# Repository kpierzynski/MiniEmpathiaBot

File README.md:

# RoboBond
## Empatyczny rój robotów

| Mobilny rój robotów |
|:-:|
||

### Motywacja
Celem projektu jest opracowanie drugiej generacji empatycznego roju robotów, umożliwiającej przeprowadzanie fizycznych eksperymentów wygodniej, szybciej i na szerszą skalę. Celem badawczym jest analiza algorytmów sztucznej empatii na zminiaturyzowanej generacji roju robotów.

### Opis
Projekt "Rój Empatycznych Robotów" polega na stworzeniu zaawansowanej grupy robotów, która będzie zdolna do interakcji i współpracy, odzwierciedlając przy tym podstawowe instynkty ludzkie, aby efektywnie rozwiązywać zadane problemy. Przyjęcie perspektywy innej osoby i próba zrozumienia jej punktu widzenia znaczenie poprawia współpracę oraz wpływa na osiągnięte wyniki. Roboty dzięki modułowi sztucznej empatii, będą mogły podejmować decyzje w oparciu o stan sąsiednich robotów, pozwala to na stworzenie bardziej efektywnych strategii i szybsze osiągnięcie globalnego celu.

Do przeprowadzenia eksperymentów walidujących użycie algorytmów sztucznej empatii, stworzone zostały dwa symulatory oraz fizyczna platforma mobilnych robotów.

### Zastosowania
- Platforma badawcza dla naukowców do weryfikacji nowych algorytmów sztucznej empatii,
- Środowisko dla nauczycieli wspierające dydaktykę z zakresu sztucznej inteligencji,
- Infrastruktura do testowania nowych ścieżek automatyzacji i robotyzacji w przedsiębiorstwach,
- ... oraz wiele innych.

### Zawartość
W repozytorium znajdują się:
- Symulatory
    - `simulators/RL_ROS_Robots`
    - `simulators/Simpathy`
- Projekt mobilnych robotów
    - `kicad_workspace/bottom` - schemat elektroniczny PCB oraz opis konstrukcji
    - `code/STM32` - kod źródłowy dolnego niskopoziomowego mikrokontrolera robota
    - `code/PI` - kod źródłowy implementujący scenariusz empatyczny 
    - `cad_models` - modele 3d części robota

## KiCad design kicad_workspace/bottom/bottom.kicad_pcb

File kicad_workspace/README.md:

# Empatyczny robot, iteracja druga

## Obecna konstrukcja PCB
Widok gory | Widok spodu
-- | --
 | 

## Architektura robota

Ze względu na minimalizację wymiarów robota, jego konstrukcja przewiduje dwie połączone nad sobą płytki drukowane. Dolna płytka będzie odpowiedzialna za interakcję z otoczeniem, a górna, za przetwarzanie informacji i podejmowanie decyzji. 

Poruszanie się robota w przestrzeni będzie realizowane przy pomocy dwóch miniaturowych silników z przekładniami firmy Pololu. Każdy z nich wyposażony jest w enkoder magnetyczny na bazie czujników efektu Hall’a TLE4946-2K, specjalnie zaprojektowanych do tego scenariusza. Obrót silników będzie dodatkowo nadzorowany przez czujniki prądu, jeden na każdy silnik, aby uzyskać dokładne sterowanie prędkością obrotową. W celu wyeliminowania strat na typowych czujnikach prądu z shunt resistor, można użyć układu, który mierzy prąd w oparciu o efekt Hall’a. Przykładem takich sensorów są ACS712 lub ACS724. Do zasilania silników jako układ wykonawczy zostanie wykorzystany DRV8833. Ten sterownik umożliwia obsługę dwóch silników i charakteryzuje się tym, że wymaga jedynie dwóch linii sterujących na silnik do regulacji prędkości i kierunku obrotu, a także jest prosty w obsłudze za pomocą sprzętowych Timer'ów w mikrokontrolerze. 

Aby zapewnić robotowi precyzyjną orientację w terenie, zostanie wyposażony w zintegrowany układ BNO055, składający się z akcelerometru, żyroskopu oraz magnetometru firmy Bosch. Układ ten będzie wspomagać algorytmy ruchu robota, aby osiągnąć maksymalną precyzję jego manewrów. Dodatkowo, sensory VL53L0X dostarczą informację o odległości przeszkód znajdujących się przed robotem. Zastosowanie tych sensorów wprowadza zwiększoną złożoność zarówno konstrukcji płytki, jak i algorytmów sterujących w porównaniu do tradycyjnych przycisków i krańcówek. Niemniej jednak ta zmiana przyczynia się do redukcji kontaktu mechanicznego z otoczeniem, co przekłada się na zminimalizowanie ryzyka uszkodzeń robota i zwiększenie jego niezawodności. 

Do zasilania robota zostaną wykorzystane dwa ogniwa litowo-jonowe INR18650-35E firmy Samsung o łącznej pojemności 7Ah. Ze względu na niewielkie rozmiary robota, w projekcie zostaną wykorzystane cylindryczne ogniwa zamiast płaskich baterii litowo-polimerowych, co wiąże się z koniecznością dodania układów zabezpieczających. Aby zapewnić bezpieczne zarządzani energią, zostanie wykorzystany układ ochrony baterii DW01 w połączeniu z tranzystorami wykonawczymi. Ten układ ma za zadanie monitorować napięcie baterii, aby nie przekroczyła dopuszczalnego zakresu oraz odłączać napięcie w przypadku wystąpienia zwarcia. Proces ładowania będzie nadzorowany przez układ TP5100, który nie tylko dostarczy do dwóch amperów prądu, ale także zapewni, że proces ładowania ogniw przebiegnie zgodnie ze specyfikacją ładowania metodą constant current constant voltage (CC CV). Jednym z założeń projektu jest możliwość ładowania robota bez ingerencji człowieka. Aby to osiągnąć, na spodzie dolnej płytki drukowanej umieszone zostaną dwa pady kontaktowe. Przy ich użyciu, robot po najechaniu na specjalną stację ładowania będzie mógł ładować baterie. To rozwiązanie jest niezwykle proste, zajmuje niewiele miejsca oraz nie wprowadza strat w przekazywaniu energii. 

Robot, pomimo niewielkich rozmiarów, będzie wyposażony w układy wymagające dużego poboru prądu. Aby sprostać ich oczekiwaniom, w projekcie zastosowane będą dwie przetwornice. Jedną o napięciu wyjściowym 5V – U3V70A, która jest w stanie podać do 10A w szczycie zapotrzebowania nawet przez kilka sekund. Druga przetwornica, tym razem dla układów zasilanych napięciem 3.3V - U7V8F3 będzie dostarczać prąd dla wszystkich czujników oraz mikrokontrolera. Warto zaznaczyć, że przetwornica 3.3V będzie pracować w dwóch trybach: step-down, gdy bateria będzie naładowana i step-up, gdy bateria będzie bliższa rozładowaniu.  

Na dolnej płytce umieszczony będzie również 32-bitowy mikrokontroler z rodziny STM32. Wysoka moc obliczeniowa, elastyczność i popularność pozwoli na implementację niemal dowolnie skomplikowanych algorytmów. Będzie on kontrolować wszystkie powyższe układy oraz komunimować się z głównym procesorem robota. 

Rolę mózgu urządzenia będzie pełnić Raspberry Pi Zero 2 W, jest to czterordzeniowy, jednopłytkowy komputer umieszczony na górnej płytce drukowanej, który z pomocą kamery Raspberry Pi Cam V3 będzie reagować na swoje otoczenie i inne roboty. Wszystkie algorytmy sztucznej inteligencji i empatii będą realizowane właśnie na tym mikrokomputerze. Sygnalizacja własnego wewnętrznego stanu będzie osiągana przez indywidualnie adresowalne diody RGB - WS2812B, ułożone w 8 rzędów, każdy po 3 diody. Umożliwi to wyświetlenie co najmniej półtora miliona różnych stanów. 

## Wstępne rozważania na temat wymagań konstrukcyjnych
- **Konstrukcja**

Robot będzie miał średnicę około 8 cm. Będzie złożony z dwóch płytek PCB, połączonych w 'kanapkę'. Dolna płytka (STM32 lub AVR) będzie odpowiadała za sterowanie silnikami itp, a górna (Rpi) od obliczenia i obsługę kamery.
Pojazd będzie wyposażony w krańcówki (switch) (około cztery sztuki) wokół swojej obudowy, aby wykrywać zderzenia z otoczeniem.

| Góra | Bok |
| -------- | -------- |
|  |  |

- **Sterowanie**

Za sterowanie czujnikami, silnikami itp. będzie odpowiedzialny mikrokontroler STM32 lub AVR. Z kolei za obsługę kamery będzie odpowiadał moduł Rasberry Pi Zero v2.

- **Napęd**

Robot będzie poruszał się z wykorzystaniem silników DC z enkoderami, aby umożliwić dokładne pomiary pojazdu. Niezbędny do tego będzie również sterownik silników, który w raz z enkoderami będzie sterowany przez STM. Dobór odpowiedniego przełożenia silnika wymaga ustalenia z jaką prędkością powinien poruszać się robot.

| Koła | Tylne koło | Silnik z enkoderem |
| -------- | -------- | -------- |
|  |  |  |

- **Kamera**

Kamera będzie osadzona statycznie przy wieży LED. Serwomechanizm dodaje niepotrzebną złożoność, robot może obrócić się cały, aby wykonać zdjęcie.

- **LED**

Wieża LED oparta będzie o diody WS2812B (lub kompatybilne), w ośmiu rzędach, po dwie lub trzy diody.

- **Zasilanie**

Do zasilania pojazdów można zastosować cylindryczną baterie litowo jonową 18650 osadzoną w środku wieży LED, lub baterię litowo polimerową. W obu przypadkach wymagany będzie jeszcze układ ładowania ogniwa.
Aby uzyskać napięcie zasilania 5V, należy zastosować przetwornicę. Możliwości są dwie: 
    - przetwornica podwyższająca napięcie
        - niższa sprawność
        - jedno ogniwo, stąd prostszy układ ładowania ogniw
    - przetwornica obniżająca napięcie
        - wyższa sprawność
        - dwa lub więcej ogniw, bardziej skomplikowany układ ładowania

| | Li-ion 18650 | Li-Po |
| -------- | -------- | -------- |
| Zalety   | Wydajność prądowa (nawet 30A) | Wydajne prądowo ogniwa są zazwyczaj duże |
| Zalety   | Tania | Gotowe zabezpieczenie przeciw rozładowaniu |
| Zalety   | Prosta wymiana w razie potrzeby | Płaska |
| Wady     | Podwyższa środek ciężkości | Trudno dostępna o wymaganych parametrach |
| Wady     | Wymaga modyfikacji wieży | Wymiary ograniczają możliwości |
| Wady     | Wymaga dodatkowego układu zabezpieczającego | - |

| Li-ion 18650 | Li-Po |
| -------- | -------- |
|  |  |

- **Ładowanie**

Do ładowania robotów zostaną wykorzystane pady kontaktowe, które będą w odpowiedni sposób wykrywane przez pojazdy. Do wypozycjonowania pojazdu względem padów można zastosować magnesy neodymowe, które naprowadzą robota wprost na pady. Pady kontaktowe mogłyby znajdować się pod obudową lub na jej boku.

- **Wybudzanie**

Mikrofon ultradźwiękowy, który ma ne celu wybudzenie robotów z trybu uśpienia. Jedna zewnętrzna płytka na arenie (np. ESP32/8266) będzie na stałe podłączona do internetu i będzie wyposażona w głośnik na ultradźwięki. Po otrzymaniu informacji po WiFi, wyemituje ona dźwięk, który wybudzi STM przez mikrofon, który z kolei wybudzi Rpi.
W przypadku niepowodzenia, można zastosować diody i fototranzystory/odborniki IR. 

- **Czujniki**

Warto wyposażyć robota w dodatkowe czujniki: *żyroskop*, *kompas* i *akcelerometr*. Umożliwią one dokładniejsze odnajdowanie się robota w przestrzeni.

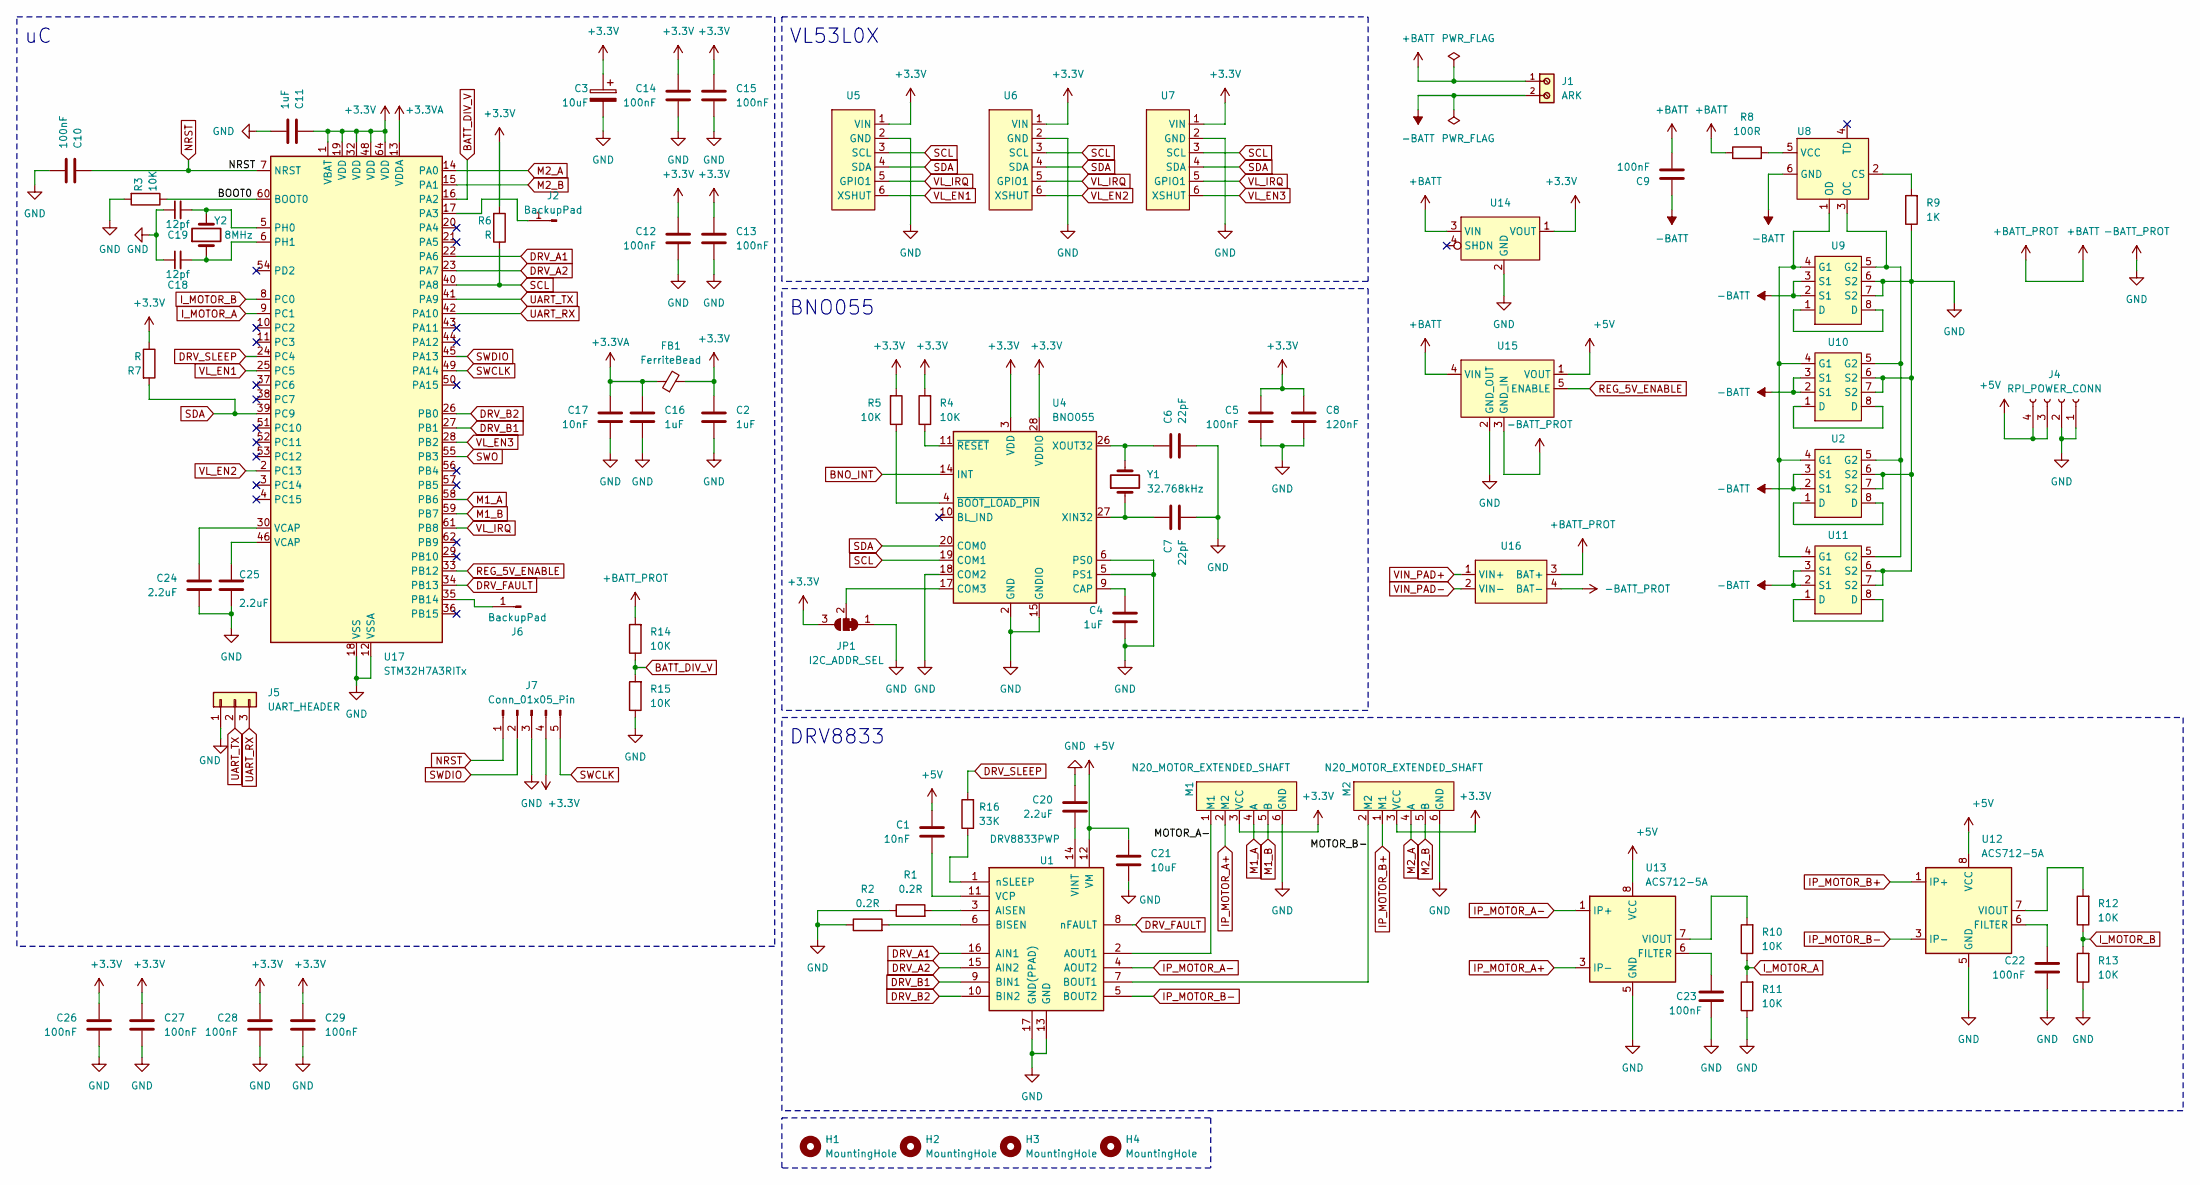
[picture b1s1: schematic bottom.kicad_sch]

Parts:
C1, C17: 10nF; C_0805_2012Metric
C2, C4, C11, C16: 1uF; C_0805_2012Metric
C3: 10uF; CP_Elec_4x3
C5, C9, C10, C12, C13, C14, C15, C22, C23, C26, C27, C28, C29: 100nF; C_0805_2012Metric
C6, C7: 22pF; C_0805_2012Metric
C8: 120nF; C_0805_2012Metric
C18, C19: 12pf; C_0805_2012Metric
C20, C24, C25: 2.2uF; C_0805_2012Metric
C21: 10uF; C_0805_2012Metric
FB1: FerriteBead; L_0805_2012Metric
H1, H2, H3, H4: MountingHole
J1: ARK; 691103110002; PART-NUMBER 691103110002
J2, J6: BackupPad; SolderWirePad_1x01_SMD_1x2mm
J4: RPI_POWER_CONN; JST_XH_B4B-XH-A_1x04_P2.50mm_Vertical
J5: UART_HEADER; PinHeader_1x03_P2.54mm_Vertical
J7: Conn_01x05_Pin; Harwin_M20-89005xx_1x05_P2.54mm_Horizontal
JP1: I2C_ADDR_SEL; SolderJumper-3_P1.3mm_Bridged12_Pad1.0x1.5mm_NumberLabels
M1, M2: N20_MOTOR_EXTENDED_SHAFT; N20_EXTENDED_SHAFT
R1, R2: 0.2R; R_0805_2012Metric
R3, R4, R5, R10, R11, R12, R13, R14, R15: 10K; R_0805_2012Metric
R6, R7: R; R_0805_2012Metric
R8: 100R; R_0805_2012Metric
R9: 1K; R_0805_2012Metric
R16: 33K; R_0805_2012Metric
U1: DRV8833PWP; TSSOP-16-1EP_4.4x5mm_P0.65mm_EP3x3mm_ThermalVias
U2, U9, U10, U11: TSSOP-8_4.4x3mm_P0.65mm
U4: BNO055; LGA-28_5.2x3.8mm_P0.5mm
U5, U6, U7: VL53L0X
U8: SOT-23-6
U12, U13: ACS712-5A; SOIC-8_3.9x4.9mm_P1.27mm
U14: S7V8F3_vertical
U15: U3V70F5
U16: TP5100
U17: STM32H7A3RITx; LQFP-64_10x10mm_P0.5mm
Y1: 32.768kHz; Crystal_SMD_MicroCrystal_CM9V-T1A-2Pin_1.6x1.0mm
Y2: 8MHz; Crystal_SMD_MicroCrystal_CM9V-T1A-2Pin_1.6x1.0mm

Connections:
+3.3V: C2.1, C3.1, C5.1, C8.1, C11.1, C12.1, C13.1, C14.1, C15.1, C26.1, C27.1, C28.1, C29.1, FB1.2, J7.4, JP1.3 (B), M1.3 (VCC), M2.3 (VCC), R4.2, R5.2, R6.2, R7.1, U4.3 (VDD), U4.28 (VDDIO), U5.1 (VIN), U6.1 (VIN), U7.1 (VIN), U14.1 (VOUT), U17.1 (VBAT), U17.19 (VDD), U17.32 (VDD), U17.48 (VDD), U17.64 (VDD)
+3.3VA: C16.1, C17.1, FB1.1, U17.13 (VDDA)
+5V: C1.1, C21.1, J4.3, J4.4, U1.12 (VM), U12.8 (VCC), U13.8 (VCC), U15.1 (VOUT)
+BATT: C9.2, J1.1, R8.1, R14.2, U14.3 (VIN), U15.4 (VIN), U16.3 (BAT+)
-BATT: C9.1, J1.2, U2.2 (S1), U2.3 (S1), U8.6 (GND), U9.2 (S1), U9.3 (S1), U10.2 (S1), U10.3 (S1), U11.2 (S1), U11.3 (S1)
-BATT_PROT: C2.2, C3.2, C4.2, C5.2, C6.2, C7.2, C8.2, C10.2, C11.2, C12.2, C13.2, C14.2, C15.2, C16.2, C17.2, C18.1, C19.1, C20.1, C21.2, C22.2, C23.2, C24.2, C25.2, C26.2, C27.2, C28.2, C29.2, J4.1, J4.2, J5.1, J7.3, JP1.1 (A), M1.6 (GND), M2.6 (GND), R1.1, R2.1, R3.2, R9.1, R11.1, R13.1, R15.1, U1.13 (GND), U1.17 (GND(PPAD)), U2.6 (S2), U2.7 (S2), U4.2 (GND), U4.5 (PS1), U4.6 (PS0), U4.15 (GNDIO), U4.16 (GNDIO), U4.18 (COM2), U4.25 (GNDIO), U5.2 (GND), U6.2 (GND), U7.2 (GND), U9.6 (S2), U9.7 (S2), U10.6 (S2), U10.7 (S2), U11.6 (S2), U11.7 (S2), U12.5 (GND), U13.5 (GND), U14.2 (GND), U15.2 (GND_OUT), U15.3 (GND_IN), U16.4 (BAT-), U17.12 (VSSA), U17.18 (VSS), U17.31 (VSS), U17.47 (VSS), U17.63 (VSS)
/BOOT0: R3.1, U17.60 (BOOT0)
/MOTOR_A-: M1.1 (M1), U1.2 (AOUT1)
BATT_DIV_V: R14.1, R15.2, U17.16 (PA2)
BNO_INT: U4.14 (INT)
DRV_A1: U1.16 (AIN1), U17.22 (PA6)
DRV_A2: U1.15 (AIN2), U17.23 (PA7)
DRV_B1: U1.9 (BIN1), U17.27 (PB1)
DRV_B2: U1.10 (BIN2), U17.26 (PB0)
DRV_FAULT: U1.8 (nFAULT), U17.34 (PB13)
DRV_SLEEP: R16.2, U17.24 (PC4)
IP_MOTOR_A+: M1.2 (M2), U13.3 (IP-), U13.4 (IP-)
IP_MOTOR_A-: U1.4 (AOUT2), U13.1 (IP+), U13.2 (IP+)
IP_MOTOR_B-: U1.5 (BOUT2), U12.3 (IP-), U12.4 (IP-)
I_MOTOR_A: R10.1, R11.2, U17.9 (PC1)
I_MOTOR_B: R12.1, R13.2, U17.8 (PC0)
M1_A: M1.4 (A), U17.58 (PB6)
M1_B: M1.5 (B), U17.59 (PB7)
M2_A: M2.4 (A), U17.14 (PA0)
M2_B: M2.5 (B), U17.15 (PA1)
NRST: C10.1, J7.1, U17.7 (NRST)
unnamed: C24.1, U17.30 (VCAP)
unnamed: C25.1, U17.46 (VCAP)
unnamed: J2.1, U17.17 (PA3)
unnamed: J6.1, U17.35 (PB14)
unnamed: JP1.2 (C), U4.17 (COM3)
unnamed: R1.2, U1.3 (AISEN)
unnamed: R2.2, U1.6 (BISEN)
unnamed: C1.2, U1.11 (VCP)
unnamed: C20.2, U1.14 (VINT)
unnamed: R16.1, U1.1 (nSLEEP)
unnamed: U2.1 (D), U2.8 (D)
unnamed: C4.1, U4.9 (CAP)
unnamed: C7.1, U4.27 (XIN32), Y1.1
unnamed: C6.1, U4.26 (XOUT32), Y1.2
unnamed: R5.1, U4.4 (~BOOT_LOAD_PIN)
unnamed: R4.1, U4.11 (~RESET)
unnamed: R9.2, U8.2 (CS)
unnamed: R8.2, U8.5 (VCC)
unnamed: U9.1 (D), U9.8 (D)
unnamed: U10.1 (D), U10.8 (D)
unnamed: U2.4 (G1), U8.1 (OD), U9.4 (G1), U10.4 (G1), U11.4 (G1)
unnamed: U2.5 (G2), U8.3 (OC), U9.5 (G2), U10.5 (G2), U11.5 (G2)
unnamed: U11.1 (D), U11.8 (D)
unnamed: C22.1, U12.6 (FILTER)
unnamed: R12.2, U12.7 (VIOUT)
unnamed: C23.1, U13.6 (FILTER)
unnamed: R10.2, U13.7 (VIOUT)
unnamed: C19.2, U17.5 (PH0), Y2.2
unnamed: C18.2, U17.6 (PH1), Y2.1
REG_5V_ENABLE: U15.5 (ENABLE), U17.33 (PB12)
SCL: R6.1, U4.19 (COM1), U5.3 (SCL), U6.3 (SCL), U7.3 (SCL), U17.40 (PA8)
SDA: R7.2, U4.20 (COM0), U5.4 (SDA), U6.4 (SDA), U7.4 (SDA), U17.39 (PC9)
SWCLK: J7.5, U17.49 (PA14)
SWDIO: J7.2, U17.45 (PA13)
SWO: U17.55 (PB3)
UART_RX: J5.3, U17.42 (PA10)
UART_TX: J5.2, U17.41 (PA9)
VIN_PAD+: U16.1 (VIN+)
VIN_PAD-: U16.2 (VIN-)
VL_EN1: U5.6 (XSHUT), U17.25 (PC5)
VL_EN2: U6.6 (XSHUT), U17.2 (PC13)
VL_EN3: U7.6 (XSHUT), U17.28 (PB2)
VL_IRQ: U5.5 (GPIO1), U6.5 (GPIO1), U7.5 (GPIO1), U17.61 (PB8)

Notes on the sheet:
DRV8833
VL53L0X
BNO055

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
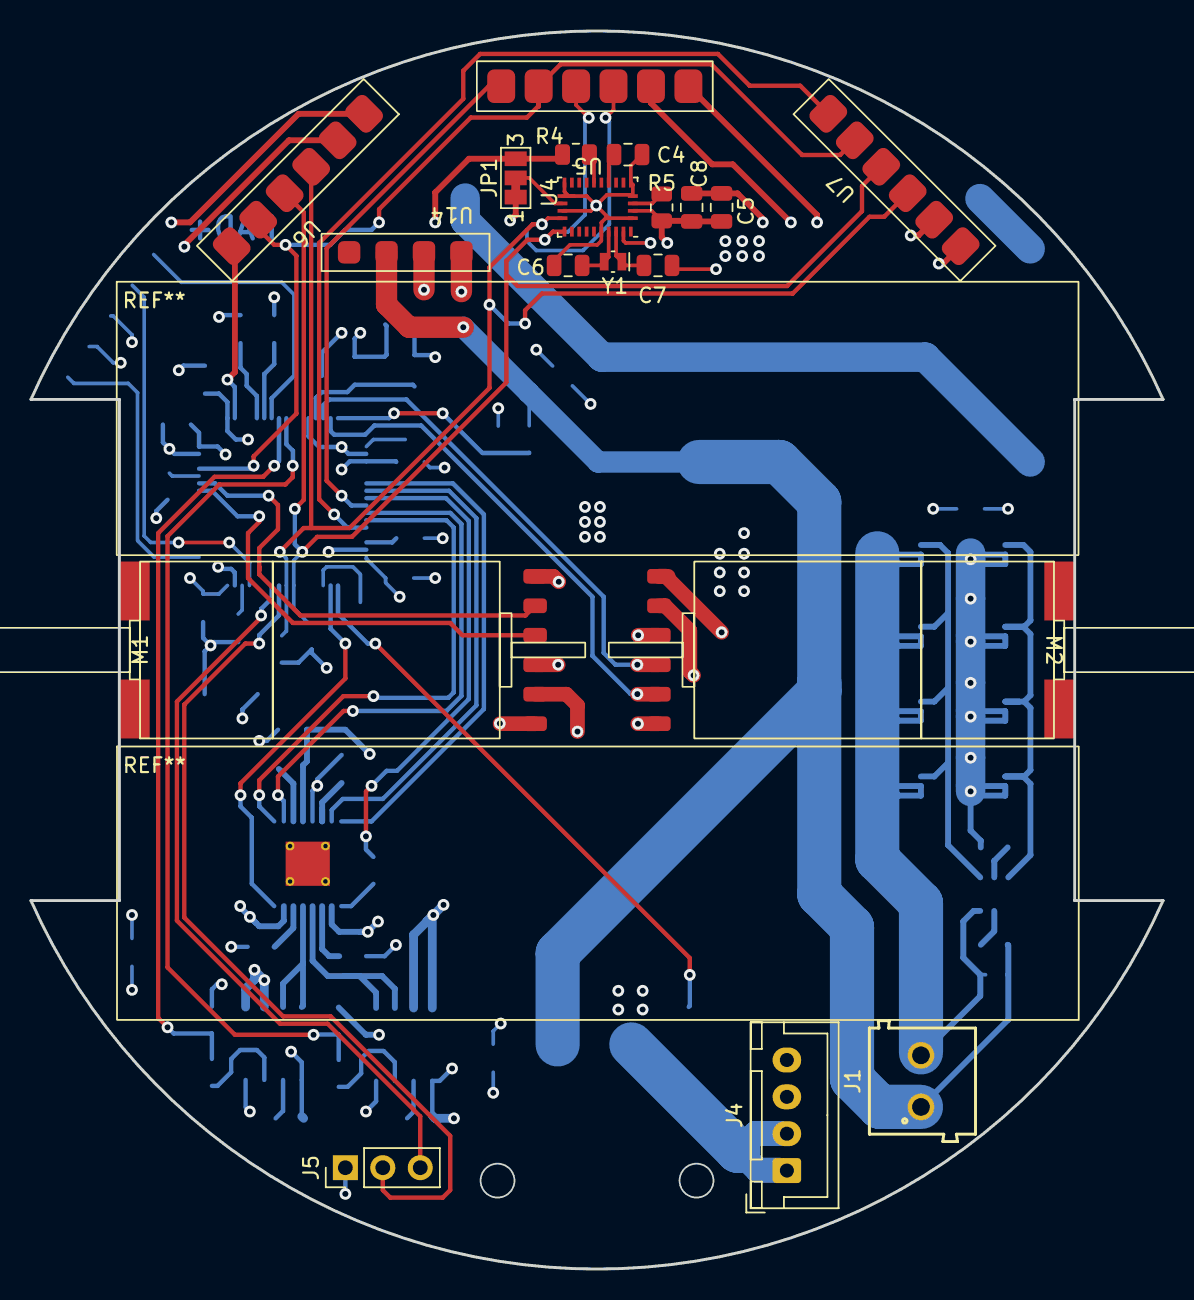
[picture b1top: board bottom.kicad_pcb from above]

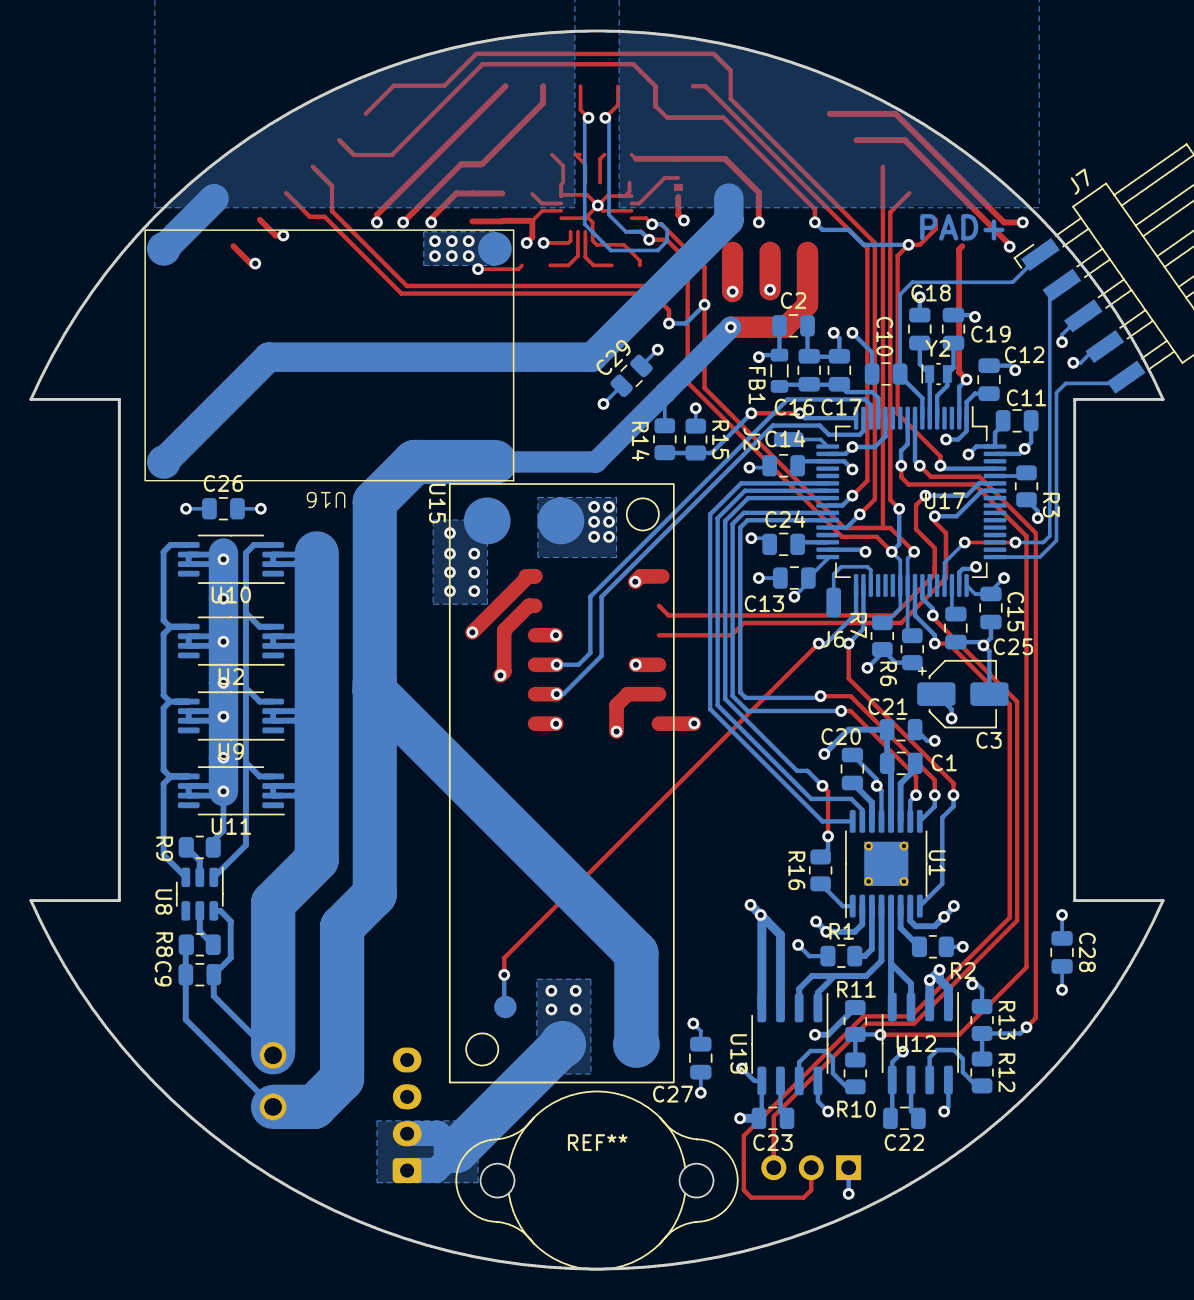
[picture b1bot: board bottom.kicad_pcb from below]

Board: 4 copper layers, 76.8 x 84.0 mm, 73 parts (54 on the bottom side), 67 nets.

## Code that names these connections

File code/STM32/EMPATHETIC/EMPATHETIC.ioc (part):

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Mcu.Name=STM32H7A3R(G-I)Tx
Mcu.Package=LQFP64
Mcu.UserName=STM32H7A3RITx
PA0.GPIOParameters=GPIO_Label
PA0.GPIO_Label=Enkoder silnika 2 Hall 1
PA0.Signal=S_TIM2_CH1_ETR
PA1.GPIOParameters=GPIO_Label
PA1.GPIO_Label=Enkoder silnika 2 Hall 2
PA1.Signal=S_TIM2_CH2
PA10.Mode=Asynchronous
PA10.Signal=LPUART1_RX
PA3.GPIOParameters=GPIO_Speed,GPIO_Label
PA3.GPIO_Label=DEBUG
PA3.GPIO_Speed=GPIO_SPEED_FREQ_MEDIUM
PA3.Signal=GPIO_Output
PA6.Signal=S_TIM3_CH1
PA7.Signal=S_TIM3_CH2
PA8.GPIOParameters=GPIO_Pu
PA8.GPIO_Pu=GPIO_PULLUP
PA8.Mode=I2C
PA8.Signal=I2C3_SCL
PA9.Mode=Asynchronous
PA9.Signal=LPUART1_TX
PB0.Signal=S_TIM3_CH3
PB1.Signal=S_TIM3_CH4
PB13.GPIOParameters=GPIO_PuPd,GPIO_Label
PB13.GPIO_Label=nFAULT
PB13.GPIO_PuPd=GPIO_PULLUP
PB13.Signal=GPIO_Input
PB14.GPIOParameters=PinState,GPIO_PuPd,GPIO_Label
PB14.GPIO_Label=nSleep
PB14.GPIO_PuPd=GPIO_NOPULL
PB14.PinState=GPIO_PIN_RESET
PB14.Signal=GPIO_Output
PB6.GPIOParameters=GPIO_Label
PB6.GPIO_Label=Enkoder silnika 1 Hall 1
PB6.Signal=S_TIM4_CH1
PB7.GPIOParameters=GPIO_Label
PB7.GPIO_Label=Enkoder silnika 1 Hall 2
PB7.Signal=S_TIM4_CH2
PB8.GPIOParameters=GPIO_Label,GPIO_ModeDefaultEXTI
PB8.GPIO_Label=VL_IRQ
PB8.GPIO_ModeDefaultEXTI=GPIO_MODE_IT_FALLING
PB8.Signal=GPXTI8
PC5.GPIOParameters=GPIO_Speed,GPIO_PuPd,GPIO_Label,GPIO_ModeDefaultOutputPP
PC5.GPIO_Label=VL_EN1
PC5.GPIO_ModeDefaultOutputPP=GPIO_MODE_OUTPUT_OD
PC5.GPIO_PuPd=GPIO_NOPULL
PC5.GPIO_Speed=GPIO_SPEED_FREQ_MEDIUM
PC5.Signal=GPIO_Output
PC9.GPIOParameters=GPIO_Pu
PC9.GPIO_Pu=GPIO_PULLUP
PC9.Mode=I2C
PC9.Signal=I2C3_SDA
RCC.SYSCLKFreq_VALUE=64000000
board=custom

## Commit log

2023-05-17 init repo with readme
2023-06-19 add document about requirements
2023-06-19 fix md preview on gitea
2023-08-09 init kicad project for bottom board. add motor symbol
2023-08-09 add gitignore, cleaning
2023-08-10 add ball caster footprint
2023-08-10 move kicad to v7. add wheel model. add wheel to motor footprint
2023-08-11 created freecad sketch for bottom pcb shape
2023-08-13 changed pcb shape dimensions. imported shape into pcb
2023-08-13 add drv8833 - motor driver
2023-08-22 add ultrasound model, footprint and symbol. add motor driver to schematic for learning kicad
2023-08-23 add example stm32 uC, add simple footprint for step-up board
2023-08-29 small updates on parts
2023-08-29 add bno055 - acc ic
2023-08-30 small schematic fixes (NC)
2023-09-04 add vl53l0x proximity/distance sensor
2023-09-05 fix vl53l0x 3d model
2023-09-05 add vl53l0x to schematic, connect footprint to sensors symbol
2023-09-05 change vcc and vdd symbols. add routes for bno055 sensor on pcb
2023-09-05 divided drv8833 and uC to separate sections
2023-09-06 add 18650 samsung li ion battery to 3d preview
2023-09-06 add battery connector
2023-09-17 update gitignore to skip lock file
2023-09-17 add dw01 ic symbol, add holes to u3v70f5
2023-09-17 add 8205a mosfet for dw01
2023-09-17 add dw01 and its mosfets to schematic and pcb
2023-09-18 wired dw01 and 4x 8205a mosfets
2023-09-18 add S7V8F3 step up/down 3.3v regulator
2023-09-19 import bq24250 symbol and footprint
2023-09-19 add 3d model to bq24250 footprint
2023-09-28 switch to stm32f303re uC
2023-09-28 initial stm and its elements placement
2023-09-28 add solder pads to motor footprint for soldering it to pcb
2023-10-01 add datasheets
2023-10-17 fix footprints 3d models paths
2023-10-17 add kibot action for 3d render
2023-10-17 allow manual gh action trigger
2023-10-17 Add current render to readme. Fix some footprint 3d model paths problems
2023-10-17 fix typo in gh action workflow
2023-10-17 clean old env path variables
2023-10-24 add file for storing power consumption measurements
2023-10-24 add rpi power consumption data
2023-10-24 add VL53L0X power consumption readings
2023-10-25 add power consumption test with aruco detection
2023-10-25 add nucleo power consumption value
2023-10-25 add step up readings (disconnected)
2023-10-31 add block_diagram image
2023-10-31 add block diagram to readme
2023-11-10 add pcb shape with holes for 3d printing prototype
2023-11-17 Add pcbs connector pinout info
2023-11-22 update block diagram
2023-11-23 add tp5100 li ion charger module
2023-11-23 add copper pads for charging
2023-11-23 changed gold-like finish on copper on renders
2023-11-27 add mounting holes and acs712 current sensors to schematic
2023-11-27 add tp5100 battery charge current values
2023-11-28 update tp5100 module footprint
2023-11-28 add all modules to pcb (except termometer)
2023-11-28 add 3.3v step-up/down module
2023-11-28 add S7V8F3 symbol, footprint. add S7V8F3 to schematic
2023-11-28 add S7V8F3 vertical footprint
2023-11-28 add U3V70F5 symbol and footprint. add it to schematic
2023-11-28 add batt_prot symbol. clean schematic
2023-11-28 changed uC to STM32H7A3RIT6
2023-11-29 changed tp5100 footprint to smd. add wiring for li-ion protection and charging
2023-11-29 wired motors
2023-11-29 prepare to wire distance sensors
2023-11-30 wired laser sensors
2023-11-30 move pcb to 4 layer. prewire all elements except signals to drv, encoders
2023-12-01 wired sensors to uC. missing bno_irq and i_motor_ab
2023-12-01 wired rest. missing rpi connector and proper battery connectors
2023-12-02 add simplified programming header for stm32
2023-12-02 add uart header for rpi
2023-12-04 add Ark connector and fix traces
2023-12-06 fix ark model and 5V trace
2023-12-07 fix ark model and gnd trace
2023-12-09 minor routes optimisation
2024-01-02 changed all blind vias to through vias (cost reduction). minor improvements. add two backup pins pads
2024-01-03 move power connector away from ball caster
2024-01-03 moved components description for better visibility
2024-02-21 fix label c27
2024-02-21 add 3.3v to programming header
2024-02-21 add text for charging pad+
2024-02-21 fix drv8833 wrong vint cap connection. connect nSleep pin to uC
2024-02-21 change j4 power connector orientation
2024-02-24 fix motors pinout
2024-02-24 add additional vias for motor pins
2024-03-07 fix traces
2024-03-12 make motor pad bigger
2024-03-12 add simple stm32cube ide project that turns motors on and read encoder
2024-03-28 add test adc project for l152 (oversampling, timer trigger, dma)
2024-03-28 add oversampled ADC triggered by TIMER (25kHz), handled by DMA
2024-04-01 add cmsis dsp library for fir adc
2024-04-24 add 3d models of utility elements
2024-04-28 tilt camera mount and widen clearance for bending camera ribbon cable
2024-05-21 add holes to rpi_board model for cables
2024-05-28 add draft of a charger station
2024-05-28 add vl53l0x sensor api
2024-05-29 add informations about main stm32 code project
2024-05-29 add projects poster
2024-05-29 add adc and fir code testing capabilities of stm32s adc
2024-05-29 add scenario simulator written in unity
2024-05-29 Create LICENSE file for Simpathy simulator
2024-05-29 Rename LICENSE to LICENSE.md
2024-05-29 add PI program to execute empathetic scenario
2024-05-29 add util script for camera and distortion matrix solver
2024-05-31 add RL ROS simulator
2024-06-03 add timer to measure elapsed time of experiment. fix ray inaccuracies bug
2024-06-05 add files for digital filter coefs and init state
2024-06-05 provide path to include libraries for windows and linux os. update readme
2024-06-05 add seed to prnd to ensure the same starting positions for egoistic and empatic trials
2024-06-06 update repo main readme. provide readme for robots construction
2024-06-08 add Robot A, B and C to simulation
2024-06-10 fix starting point for Robot C
2024-10-29 add tweaks
2024-10-30 rewrite logic to vectors
2024-12-21 add more detailed description of a project with images
2024-12-21 improve description
2024-12-22 update description in docs
2024-12-23 add web front for camera preview. add code for streaming video feed over api
